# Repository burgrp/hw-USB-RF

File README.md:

# hw-USB-RF
RF ISM USB receiver

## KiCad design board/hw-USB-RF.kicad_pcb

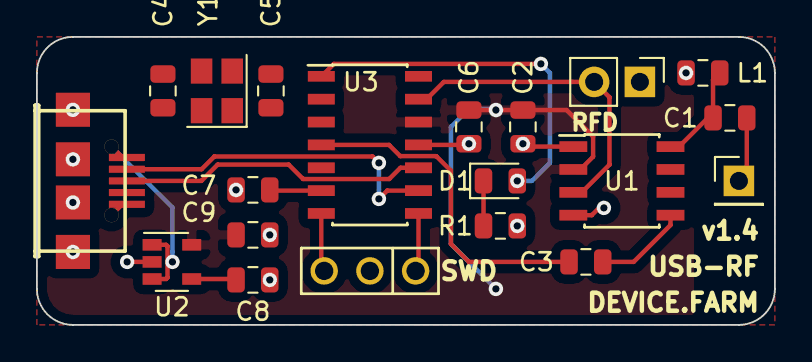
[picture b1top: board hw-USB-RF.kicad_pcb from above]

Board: 2 copper layers, 41.0 x 16.0 mm, 20 parts (0 on the bottom side), 18 nets.

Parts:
AE1: Antenna; PinHeader_1x01_P2.54mm_Vertical
C1: 2.7p; C_0805_2012Metric
C2, C3, C6, C7: 100n; C_0805_2012Metric
C4, C5: 15p; C_0805_2012Metric
C8: 10n; C_0805_2012Metric
C9: 1u; C_0805_2012Metric
D1: LED; LED_0805_2012Metric
J1: USB_OTG; conn_usb_B_micro_smd-2
L1: 33nH; L_0805_2012Metric
R1: 270R; R_0805_2012Metric
TP1: TestPoint_2Pole; PinHeader_1x02_P2.54mm_Vertical
U1: CMT2210L; SOIC-8_3.9x4.9mm_P1.27mm
U2: SPX3819; SOT-23-5
U3: ATSAMD11C14A-SS; SOIC-14_3.9x8.7mm_P1.27mm
X1: SWD
Y1: 12MHz; Crystal_SMD_3225-4Pin_3.2x2.5mm

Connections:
+3V3: C2.2, C6.1, C9.1, U1.2, U2.5, U3.12
+5V: J1.1, U2.1, U2.3
/27M138: C3.2, U3.4
/LED: D1.2, U3.1
/RF_DATA: TP1.2, U1.3, U3.13
/SWCLK: U3.7, X1.3
/SWDIO: U3.8, X1.1
/USB_DM: J1.2, U3.9
/USB_DP: J1.3, U3.10
GND: C2.1, C4.1, C5.1, C6.2, C7.2, C8.2, C9.2, J1.5, J1.6, L1.1, R1.2, TP1.1, U1.1, U1.4, U2.2, U3.11, X1.2, Y1.2, Y1.4
unnamed: AE1.1, C1.2
unnamed: C1.1, L1.2, U1.8
unnamed: C3.1, U1.5
unnamed: C4.2, U3.3, Y1.3
unnamed: C5.2, U3.2, Y1.1
unnamed: C7.1, U3.6
unnamed: C8.1, U2.4
unnamed: D1.1, R1.1
